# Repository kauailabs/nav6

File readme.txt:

The nav6 project contains the following components:

schematics:

- board schematics (developed in Eagle 6.4.0, freely available at http://www.cadsoftusa.com/)

arduino:

- As the nav6 behaves almost exactly like an Arduino UNO Rev 3 board, it can be programmed via the Arduino IDE, freely available at www.arduino.cc.  This directory contains the source code that can be built and downloaded to the nav6 via the Arduino IDE.

NOTE:  To interface to the nav6 from a computer without a RS-232 serial port, you can use an inexpensive USB-to-RS-232 converter cable such as found at http://www.iogear.com/product/GUC232A/.

crio:

- This directory contains code compatible with the 2013 version of the Java and C++ WPI Libraries, which runs in on the FIRST robotics cRio platform.  This code allows cRio-hosted code to acquire yaw/pitch/roll values from the board in real-time.

Usage Note:  As currently implemented, the nav6 must be held still for about 20 seconds after it is first powered on, during which time the nav6 is calibrating.  After that point, the yaw, pitch and roll values can be used.  This works out well for FIRST robotics competition matches, as the robot is turned on at least 20 seconds before each match starts.

docs:

- This directory contains various and sundry documentation files for third party components used in the nav6 IMU.

images:

- This directory contains source and rendered images used in the nav6 Wiki.

enclosure:

- This directory contains design files for a 3d-printed enclosure for the nav6 IMU.

production:

- This directory contains files need for production of the nav6 IMU.

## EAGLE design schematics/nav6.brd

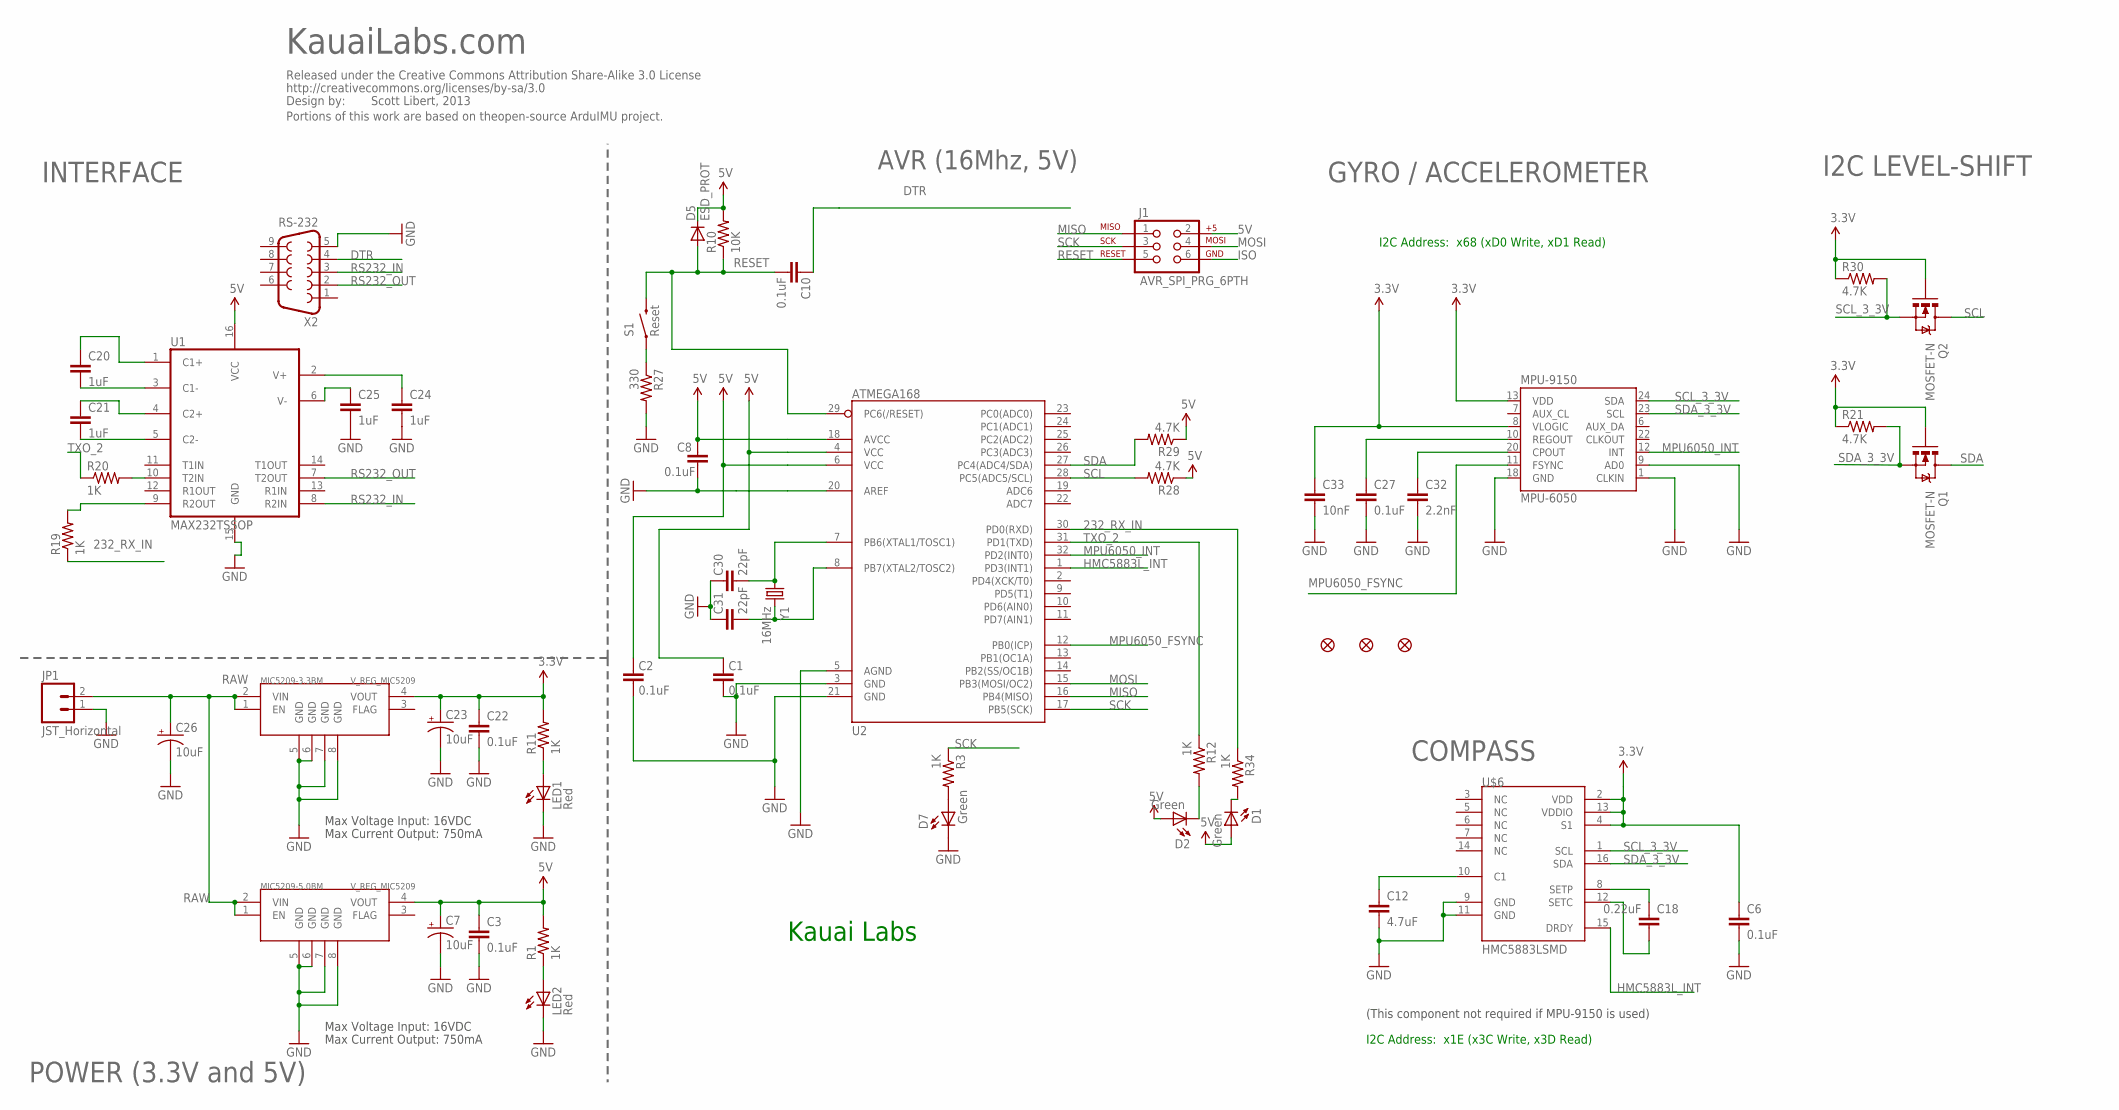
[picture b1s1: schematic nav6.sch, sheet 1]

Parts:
C1, C2, C3, C8, C10, C22, C27: 0.1uF; 0805
C6: 0.1uF; 0805; DIGIKEY# 445-3462-1-ND
C7, C23, C26: 10uF; EIA3216
C12: 4.7uF; 0805; DIGIKEY# 445-3457-1-ND
C18: 0.22uF; 0805; DIGIKEY# 445-1350-1-ND
C20, C21, C24, C25: 1uF; 0805
C30, C31: 22pF; 0805
C32: 2.2nF; 0805
C33: 10nF; 0805
D1, D2, D7: Green; LED-1206
D5: ESD_PROT; SOD-323
J1: AVR_SPI_PRG_6PTH; 2X3
JP1: JST_Horizontal; JST-2-SMD
JP2, JP3, JP4: FIDUCIAL1.5X3; FIDUCIAL-1.5X3
LED1, LED2: Red; LED-1206
MIC5209-3.3BM, MIC5209-5.0BM: V_REG_MIC5209; MSOP8
MPU-9150: MPU-6050; QFN24_INVENSENSE
Q1, Q2: MOSFET-N; SOT323
R1, R3, R11, R12, R19, R20, R34: 1K; 0805
R10: 10K; 0805
R21, R28, R29, R30: 4.7K; 0805
R27: 330; 0805
S1: Reset; TACTILE_SWITCH_SMD
U1: MAX232TSSOP; TSSOP16
U2: ATMEGA168; TQFP32-08
U$1: CREATIVE_COMMONS
U$6: HMC5883LSMD; 16LPCC; DIGIKEY# 342-1082-1-ND
X2: RS-232; DB9
Y1: 16MHz; CRYSTAL-TXC-7A

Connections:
3.3V: C6.1, C22.1, C23.A (+), C33.1, MIC5209-3.3BM.4 (VOUT), MPU-9150.8 (VLOGIC), MPU-9150.13 (VDD), Q1.1 (G), Q2.1 (G), R11.2, R21.1, R30.1, U$6.2 (VDD), U$6.4 (S1), U$6.13 (VDDIO)
5V: C1.2, C2.2, C3.1, C7.A (+), C8.2, D1.A, D2.A, D5.1 (C), J1.2, MIC5209-5.0BM.4 (VOUT), R1.2, R10.2, R28.1, R29.1, U1.16 (VCC), U2.4 (VCC), U2.6 (VCC), U2.18 (AVCC)
232_RX_IN: R19.1, R34.1, U2.30 (PD0(RXD))
DTR: C10.2, X2.4
HMC5883L_INT: U2.1 (PD3(INT1)), U$6.15 (DRDY)
ISO: C1.1, C2.1, C3.2, C6.2, C7.C (-), C8.1, C12.2, C22.2, C23.C (-), C24.2, C25.2, C26.C (-), C27.2, C30.2, C31.2, C32.2, C33.2, D7.C, J1.6, JP1.1, LED1.C, LED2.C, MIC5209-3.3BM.5 (GND), MIC5209-3.3BM.6 (GND), MIC5209-3.3BM.7 (GND), MIC5209-3.3BM.8 (GND), MIC5209-5.0BM.5 (GND), MIC5209-5.0BM.6 (GND), MIC5209-5.0BM.7 (GND), MIC5209-5.0BM.8 (GND), MPU-9150.1 (CLKIN), MPU-9150.9 (AD0), MPU-9150.18 (GND), R27.2, U1.15 (GND), U2.3 (GND), U2.5 (AGND), U2.20 (AREF), U2.21 (GND), U$6.9 (GND), U$6.11 (GND), X2.5
MISO: J1.1, U2.16 (PB4(MISO))
MOSI: J1.4, U2.15 (PB3(MOSI/OC2))
MPU6050_FSYNC: MPU-9150.11 (FSYNC), U2.12 (PB0(ICP))
MPU6050_INT: MPU-9150.12 (INT), U2.32 (PD2(INT0))
unnamed: C30.1, U2.7 (PB6(XTAL1/TOSC1)), Y1.P$1 (1)
unnamed: C32.1, MPU-9150.20 (CPOUT)
unnamed: LED2.A, R1.1
unnamed: C18.2, U$6.8 (SETP)
unnamed: C18.1, U$6.12 (SETC)
unnamed: C12.1, U$6.10 (C1)
unnamed: D1.C, R34.2
unnamed: D7.A, R3.2
unnamed: D2.C, R12.2
unnamed: C24.1, U1.2 (V+)
unnamed: C25.1, U1.6 (V-)
unnamed: LED1.A, R11.1
unnamed: C20.1, U1.1 (C1+)
unnamed: C20.2, U1.3 (C1-)
unnamed: C21.1, U1.4 (C2+)
unnamed: C21.2, U1.5 (C2-)
unnamed: C27.1, MPU-9150.10 (REGOUT)
unnamed: R19.2, U1.9 (R2OUT)
unnamed: R20.2, U1.10 (T2IN)
unnamed: R27.1, S1.1
unnamed: C31.1, U2.8 (PB7(XTAL2/TOSC2)), Y1.P$2 (2)
RAW: C26.A (+), JP1.2, MIC5209-3.3BM.1 (EN), MIC5209-3.3BM.2 (VIN), MIC5209-5.0BM.1 (EN), MIC5209-5.0BM.2 (VIN)
RESET: C10.1, D5.2 (A), J1.5, R10.1, S1.3 (2), U2.29 (PC6(/RESET))
RS232_IN: U1.8 (R2IN), X2.3
RS232_OUT: U1.7 (T2OUT), X2.2
SCK: J1.3, R3.1, U2.17 (PB5(SCK))
SCL: Q2.3 (D), R28.2, U2.28 (PC5(ADC5/SCL))
SCL_3_3V: MPU-9150.23 (SCL), Q2.2 (S), R30.2, U$6.1 (SCL)
SDA: Q1.3 (D), R29.2, U2.27 (PC4(ADC4/SDA))
SDA_3_3V: MPU-9150.24 (SDA), Q1.2 (S), R21.2, U$6.16 (SDA)
TXO_2: R12.1, R20.1, U2.31 (PD1(TXD))

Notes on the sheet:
Max Voltage Input: 16VDC
Max Current Output: 750mA
AVR (16Mhz, 5V)
INTERFACE
POWER (3.3V and 5V)
Kauai Labs
I2C LEVEL-SHIFT
GYRO / ACCELEROMETER
I2C Address: x68 (xD0 Write, xD1 Read)
(This component not required if MPU-9150 is used)
COMPASS
I2C Address: x1E (x3C Write, x3D Read)
KauaiLabs.com
Scott Libert, 2013
Portions of this work are based on theopen-source ArduIMU project.

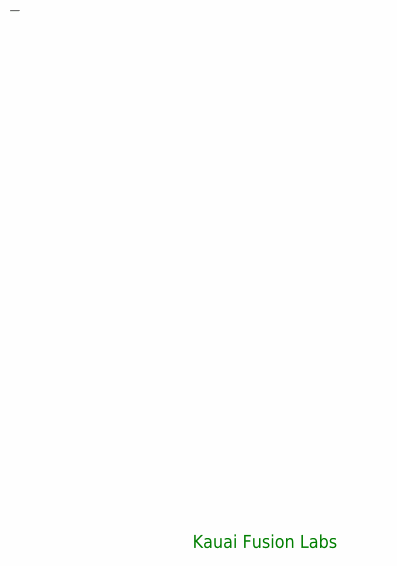
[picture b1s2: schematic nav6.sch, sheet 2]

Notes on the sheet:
Kauai Fusion Labs

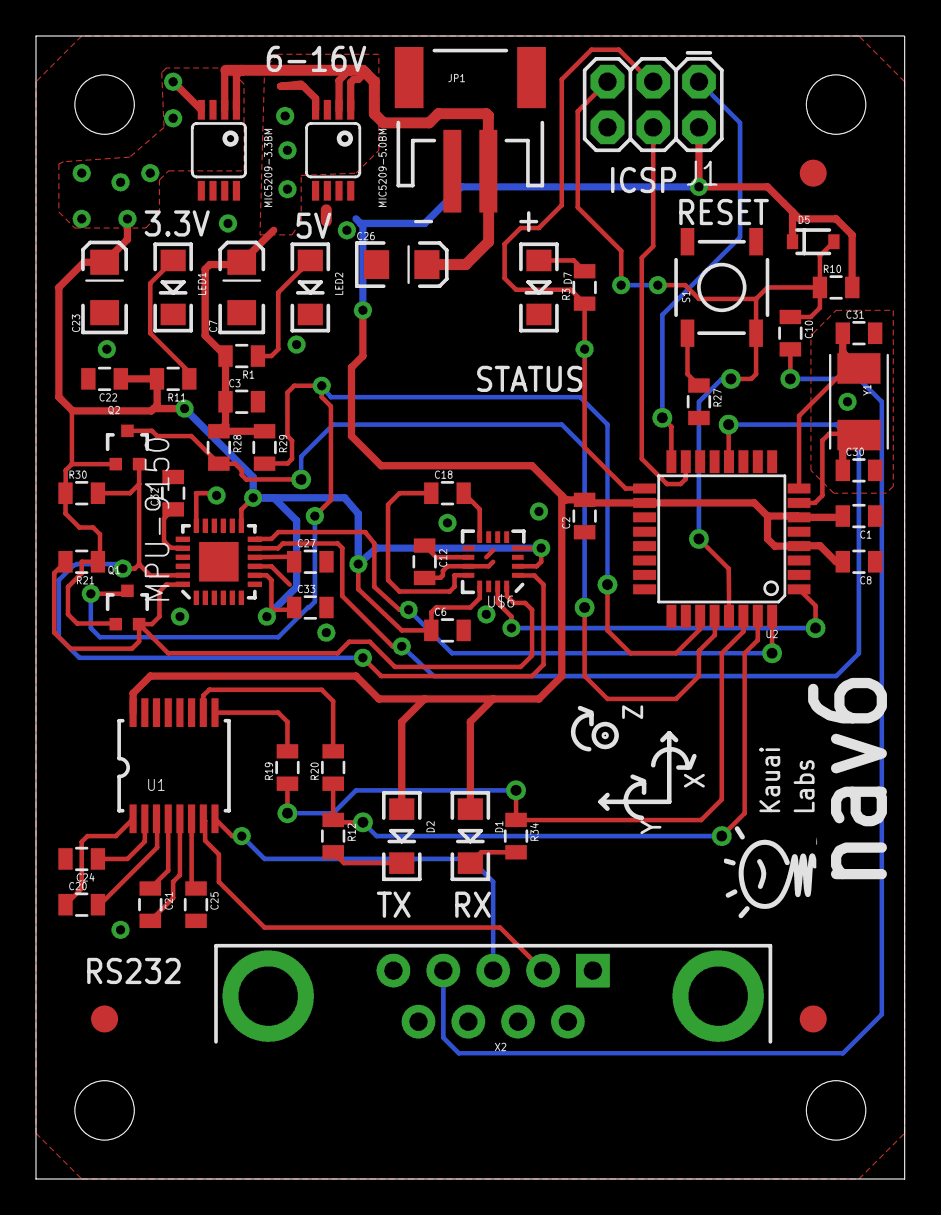
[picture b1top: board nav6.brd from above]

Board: 2 copper layers, 48.3 x 63.5 mm, 61 parts (0 on the bottom side), 41 nets.

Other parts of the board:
U$2, U$3, U$4, U$8: STAND-OFF

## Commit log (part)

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2014-01-02 Edited wiki page ProtocolAdvanced through web user interface.
2014-01-03 Updated nav6UI image with latest code
2014-01-03 Added
2014-01-03 Updated license text
2014-01-03 Added new IMUAdvanced class
2014-01-03 Created
2014-01-03 Edited wiki page TableOfContents through web user interface.
2014-01-03 Edited wiki page MotionDetection through web user interface.
2014-01-03 Edited wiki page IMUClass through web user interface.
2014-01-03 Edited wiki page IMUAdvancedClass through web user interface.
2014-01-03 Added licensing description
2014-01-03 Edited wiki page FRCRobotInstallation through web user interface.
2014-01-03 Edited wiki page nav6UI through web user interface.
2014-01-03 Edited wiki page Purchasing through web user interface.
2014-01-03 Added #defines for the nav6 Flags
2014-01-03 Updated to latest version of nav6.jar
2014-01-03 Improved icon appearance
2014-01-03 Added Label
2014-01-05 removed mpu6050 library
2014-01-05 removed historical nav6 code
2014-01-06 Removed
2014-01-06 Tagging the 1.0 release of the 'nav6' project
2014-01-07 Edited wiki page FactoryTestProcedure through web user interface.
2014-01-07 Edited wiki page Orientation through web user interface.
2014-01-07 Edited wiki page Specification through web user interface.
2014-01-07 Edited wiki page YawDrift through web user interface.
2014-01-07 Edited wiki page References through web user interface.
2014-01-07 Cleaned up code/comments. Added nav6 status led updating code in case of failure to intialize. Increased number of i2c bits clocked during I2C reset. Added calculation of world linear acceleration to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
2014-01-07 updated to latest nav6.jar
2014-01-07 Added display of world linear acceleration in Z Axis
2014-01-07 Deleted tag - cut too early...
2014-01-08 Fixed bug in IMU class constructor; modified Thread constructor invocation to take 'this' (IMU class instance reference) as a paramter
2014-01-08 updated to latest build of nav6.jar
2014-01-09 Compressed nav6 purple jpg
2014-01-09 Added small purple jpg
2014-01-09 removed larger image
2014-01-09 reduced size
2014-01-09 Added new 'Gyro' Update message'
2014-01-09 Added Support for new 'Gyro' update message
2014-01-09 Modified to match renamed message ID for the quaternion update message
2014-01-09 Updated nav6.jar file
2014-01-09 Created release 2.1 tag
2014-01-09 Create 2.1 Release tag
2014-01-09 Deleted incorrect tag references.
2014-01-09 Recreated 2.1 release tag
2014-01-10 Added 'update rate' to Stream Configuration Command
2014-01-10 modified to use the new 'update rate' parameter in the stream configuration command
2014-01-10 Recreated 2.1 tag
2014-01-12 Fixed bugs in code/comments regarding the type of update message used in basic and advanced cases
2014-01-12 modifed setDTR() parameter from false to true, to help avoid issues experienced when resetting the nav6 Atmega processor [the MPU6050 sometimes hangs on re-initialization] via the Serial port DTR lin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
2014-01-12 updated nav6.jar library to latest build
2014-01-13 Edited wiki page Acknowledgements through web user interface.
2014-01-14 Updated to build properly with J2ME and JDK 1.4
2014-01-14 Deleted
2014-01-14 Updated to compile for J2ME and JDK1.4
2014-01-14 Updated to use newer version of nav6.jar which compiles for J2ME and JDK1.4
2014-01-14 renamed GetXXX() functions to getXXX(), to conform to java method naming standards
2014-01-14 Refactored to use new J2ME-compliant version of nav6.jar
2014-01-14 Updated to latest (J2ME-compliant, JDK1.4 compatible) nav6.jar
2014-01-18 Fixes based on issues found/reported by Will Marshall (Team 11). Fixed bug in initIMU to ensure world linear history was initialized. Modified visibility of certain methods. Refactored run() methods 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
2014-01-18 Added while loop to code that updates dashboard in teleop, based on issue found/reported by Will Martin (Team 11).
2014-01-18 Updated auto-modified Netbeans project file
2014-01-18 Updated to latest build of nav6.jar file
2014-01-19 Added/integrated new BufferedSerialPort class to work around issues w/receive buffer size in the WPILibrary SerialPort class
2014-01-20 Added code to IMU.java to reset the serial port in case garbage is received; this case is seen sometimes and needs to be cleared.
2014-01-20 Modified to add more delay between dashboard updates.
2014-01-20 Updated to latest build including fixes to IMU.java to deal with serial port issues
2014-01-20 Added Beta Release of YPR Mode nav6 Labview interface code, developed by Joe Ross
2014-01-20 Added support for waiting 2 seconds, then sending stream configuration request. Also, added code to IMUAdvanced to mirror IMU, resetting the serial port if it gest into a bad state. Also, removed the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
2014-01-20 Updated java sample code after testing w/latest IMU and IMU Advanced classes.
2014-01-20 Added code to handle cases where contact is lost w/the nav6; the thread run() method periodically checks to see if new data has arrived. If so, it sends out the stream reconfiguration message.
2014-01-20 Fixed bugs related to chagnes in the C++ version of the WPI Library and/or the VISA layer that was causing exceptions when high data rates (100hz) are used. Also updated to match the code in the Java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
2014-01-21 Moving files to nav6SimpleRobotExample subdirectory
2014-01-21 Added new nav6SimpleRobotExmample code
2014-01-21 Latest updates from Joe Ross, as of 7 p.m., 1/20/2014
2014-01-21 Added Errata Directory
2014-01-21 Added new images in support of errata documentation
2014-01-21 Edited wiki page Troubleshooting through web user interface.
2014-01-21 Fixed bug by adding call of UpdateYawHistory() from within the IMUAdvanced class
2014-01-21 Fixed issue with updating of yaw history from within IMUAdvanced class
2014-01-21 Updated nav6.jar to latest build
2014-01-21 Fixed some bugs in the IMUAdvanced class
2014-01-21 Modified decodeQuaternion function to use signed rather than unsigned values for the quaternion and accelerometer data.
2014-01-22 essage
2014-01-22 Added code to re-send the stream configuration request if a stream config response is not received within 3 seconds of the last attempt.
2014-01-22 Updated sample code to wait until calibration is complete and then zero the yaw
2014-01-22 Updated nav6.jar to latest buildt
2014-01-23 Recover from cable disconnect or power outage. Reduce CPU usage with low update rates. Fix application build error.
2014-01-23 Fixed IsCalibrating() to work correctly; added it to the simple robot program
2014-01-23 Moved IsCalibrating() method to base IMU class.
2014-01-25 Latest checkin from Joe Ross; includes API documentation
2014-01-25 Initial checkin
2014-01-25 Latest Build
2014-01-26 Removed temporary directory
2014-01-26 Removed temporary files
2014-01-27 Edited wiki page FAQ through web user interface.
2014-01-27 Edited wiki page FieldOrientedDriveExample through web user interface.
2014-01-29 Optimized performance, cleaned up documentation
2014-01-29 Modified to use isCalibration() for IMU class, now that this method is in the base class
2014-01-29 Fixed a few issues reported by Will Martin
2014-01-29 Modified to match modified IMUProtocol interface changes
2014-01-29 Updated to latest library
2014-01-29 Updated to match changes in interface to IMUProtocol class
2014-01-31 Edited wiki page Java through web user interface.
2014-01-31 Edited wiki page Labview through web user interface.
2014-01-31 Edited wiki page Cplusplus through web user interface.
2014-01-31 Refactored to match Java code
2014-02-01 Added new STEP files and PNGs
2014-02-01 Added description of new STEP files
2014-02-01 Fixed bug that was causing crashes when connection was lost
2014-02-04 Added additional error handling, to handle cases where nav6 is unplugged at beginning of match (previously, this could lead to cases where the robot is unresponsive.
2014-02-04 Edited wiki page Customization through web user interface.
2014-03-07 Edited wiki page SensorCalibration through web user interface.
2014-05-23 Added PNG version of the schematic
2014-12-02 Added Java IMU class, which has been tested w/the new RoboRIO Beta WPI Libraries. Modification/testing performed by Joe Ross.
2015-01-04 Adding RoboRio-ported versions of the LabView, C++ and Java client-side libraries and sample code for a FRC Robot.
2015-01-04 Removed a navx-mxp file from the nav6 sample code.
2015-03-14 Create gh-pages branch via GitHub
2015-03-14 Migrating wiki contents from Google Code
2015-12-30 made constant time normalization
2016-01-15 created vi lib
2016-01-15 vi package edited
2016-02-16 made raw yaw absolute

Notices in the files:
parts and their libraries:
SparkFun: Released under the Creative Commons Attribution Share-Alike 3.0 License
SparkFun: http://creativecommons.org/licenses/by-sa/3.0
SparkFun-DigitalIC: Licensing: CC v3.0 Share-Alike You are welcome to use this library for commercial purposes.
